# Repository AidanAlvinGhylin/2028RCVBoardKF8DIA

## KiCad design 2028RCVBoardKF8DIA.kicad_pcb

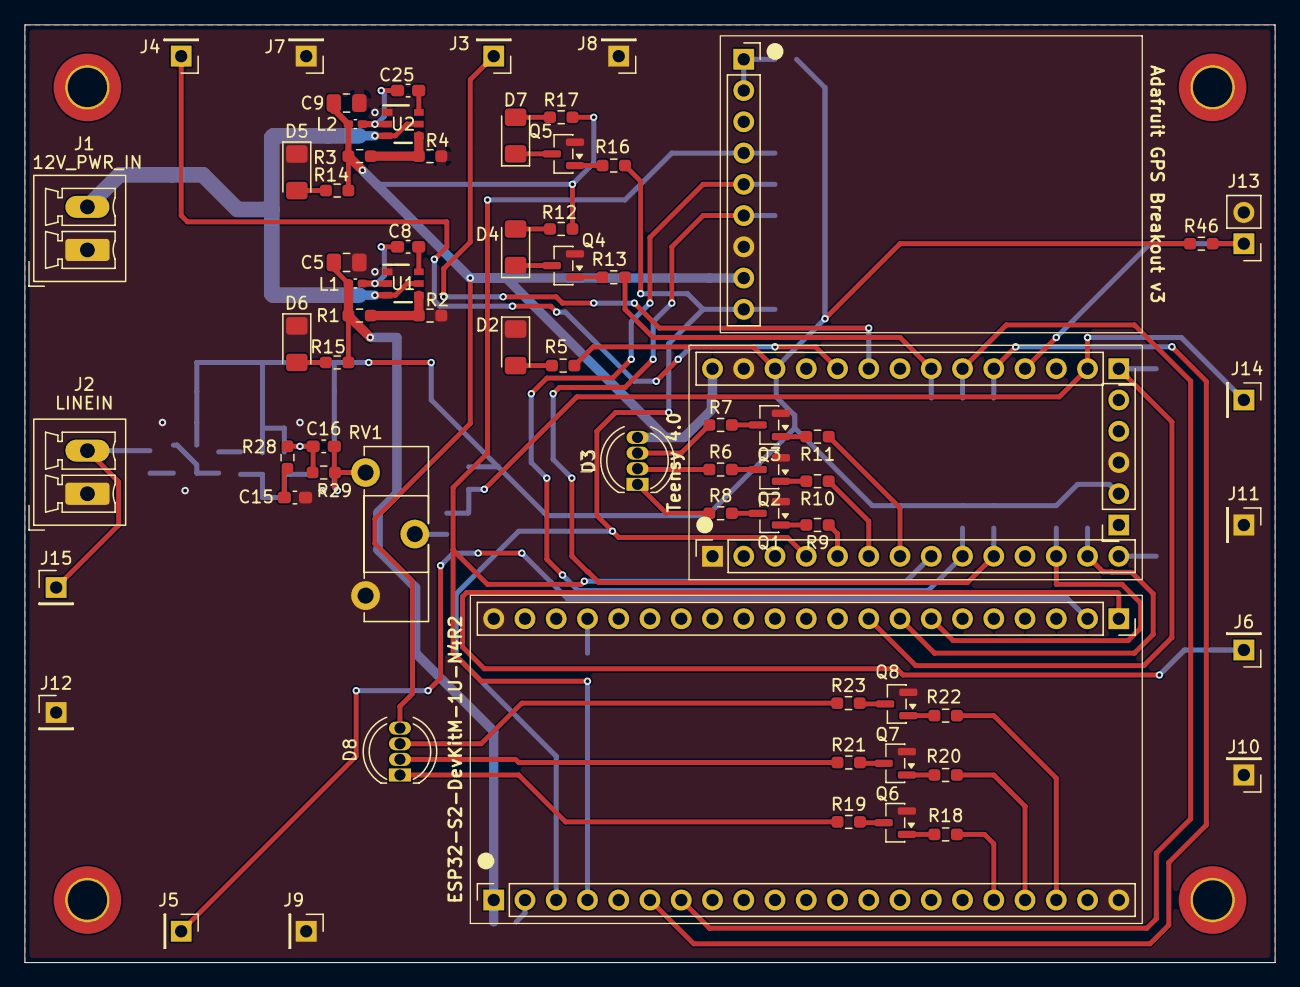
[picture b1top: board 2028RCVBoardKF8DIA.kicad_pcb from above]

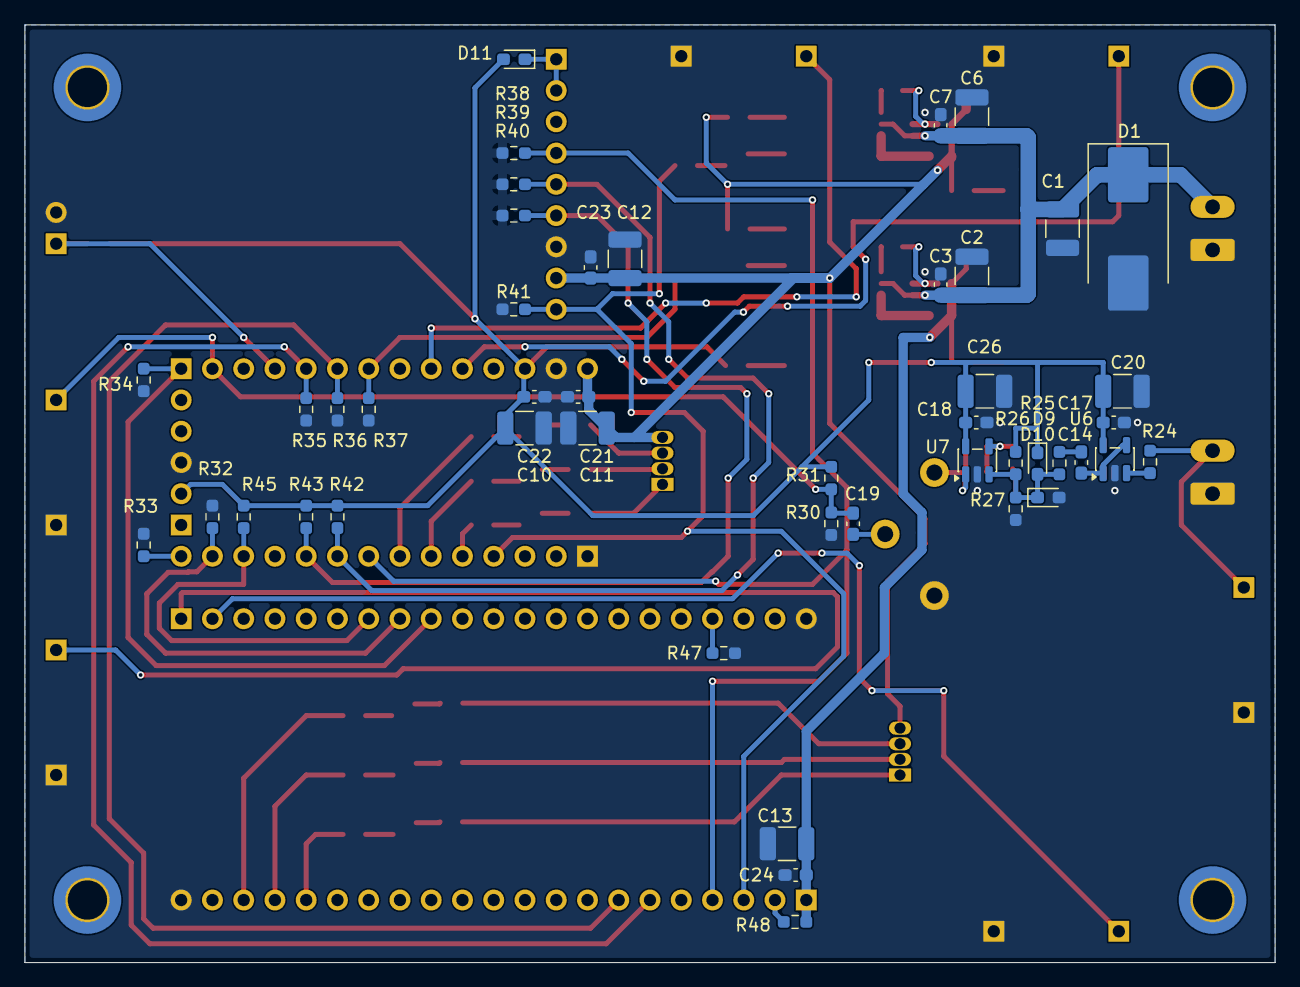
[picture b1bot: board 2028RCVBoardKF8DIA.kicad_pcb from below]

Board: 2 copper layers, 101.6 x 76.2 mm, 116 parts (46 on the bottom side), 73 nets.

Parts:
C1, C2, C6, C10, C11, C12, C13: 47uF; C_1210_3225Metric_Pad1.33x2.70mm_HandSolder
C3, C7, C8, C21, C22, C23, C24, C25: 0.1uF; C_0603_1608Metric_Pad1.08x0.95mm_HandSolder
C5, C9: 22uF; C_0805_2012Metric_Pad1.18x1.45mm_HandSolder
C14, C15, C19: 10uF; C_0603_1608Metric_Pad1.08x0.95mm_HandSolder
C16: 10nF; C_0603_1608Metric_Pad1.08x0.95mm_HandSolder
C17, C18: 100nF; C_0603_1608Metric_Pad1.08x0.95mm_HandSolder
C20, C26: 4.7uF; C_1210_3225Metric_Pad1.33x2.70mm_HandSolder
D1: D; D_SMC_Handsoldering
D2: 3V3_TNSY LED; LED_1206_3216Metric_Pad1.42x1.75mm_HandSolder
D3: Teensy Indicator LED; LED_D5.0mm-4_RGB
D4: GPS_LOCK LED; LED_1206_3216Metric_Pad1.42x1.75mm_HandSolder
D5: 5V LED; LED_1206_3216Metric_Pad1.42x1.75mm_HandSolder
D6: 3V3 LED; LED_1206_3216Metric_Pad1.42x1.75mm_HandSolder
D7: LED; LED_1206_3216Metric_Pad1.42x1.75mm_HandSolder
D8: ESP Indicator LED; LED_D5.0mm-4_RGB
D9, D10, D11: D_Schottky; D_0603_1608Metric_Pad1.05x0.95mm_HandSolder
J1: 12V_PWR_IN; PhoenixContact_MCV_1,5_2-G-3.5_1x02_P3.50mm_Vertical
J2: LINEIN; PhoenixContact_MCV_1,5_2-G-3.5_1x02_P3.50mm_Vertical
J3, J4, J5, J6, J7, J8, J9, J10, J11, J12, J14, J15: Conn_01x01; PinHeader_1x01_P2.54mm_Vertical
J13: Conn_01x02; PinHeader_1x02_P2.54mm_Vertical
L1, L2: 1.5uH; L_0402_1005Metric_Pad0.77x0.64mm_HandSolder
Q1, Q2, Q3, Q4, Q5, Q6, Q7, Q8: 2N7002; SOT-23
R1: 470; R_0603_1608Metric_Pad0.98x0.95mm_HandSolder
R2, R4: 100; R_0603_1608Metric_Pad0.98x0.95mm_HandSolder
R3, R6, R21, R29: 750; R_0603_1608Metric_Pad0.98x0.95mm_HandSolder
R5, R17: 2.2k; R_0603_1608Metric_Pad0.98x0.95mm_HandSolder
R7, R23: 220; R_0603_1608Metric_Pad0.98x0.95mm_HandSolder
R8, R19: 536; R_0603_1608Metric_Pad0.98x0.95mm_HandSolder
R9, R10, R11, R13, R16, R18, R20, R22, R30, R31, R32, R33, R34, R35, R36, R37, R38, R39, R40, R41, R42, R43, R45, R46, R47, R48: 10k; R_0603_1608Metric_Pad0.98x0.95mm_HandSolder
R12, R14, R15: 3.3k; R_0603_1608Metric_Pad0.98x0.95mm_HandSolder
R24, R25, R28: 1k; R_0603_1608Metric_Pad0.98x0.95mm_HandSolder
R26, R27: 240k; R_0603_1608Metric_Pad0.98x0.95mm_HandSolder
RV1: 1k; Potentiometer_ACP_CA14-H4_Horizontal
U1, U2: TPS563249DDCR; DDC0006A_L
U3: Teensy4.0_THT
U4: AdafruitGPSBreakoutv3_THT
U5: ESP32-S2-DevKitM-1U-N4R2
U6, U7: LT6015xS5; SOT-23-5

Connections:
3V3_GPS: D11.1 (K), U4.1 (3V3), U4.2 (EN)
3V3_TNSY: C10.2, C17.2, C18.2, C20.2, C22.2, C26.2, D9.1 (K), D11.2 (A), R5.1, R26.2, R31.2, R42.1, R43.1, R45.1, R46.1, U3.26 (3V3), U3.30 (3V3), U6.5 (V+), U7.5 (V+)
+3.3V: C5.1, C13.1, C24.1, L1.2, R1.1, R15.1, R48.1, U5.1 (3V3)
+5V: C9.1, C11.2, C12.1, C21.2, C23.1, D3.4 (BA), D8.4 (BA), L2.2, R3.1, R12.1, R14.1, R17.1, U3.28 (VIN), U4.8 (VIN)
+12V: C1.1, C2.1, C3.1, C6.1, C7.1, D1.1 (K), J1.2, U1.3 (VIN), U1.5 (EN), U2.3 (VIN), U2.5 (EN)
ADC_IN: C19.2, J14.1 (Pin_1_1), R30.2, R31.1, U3.16 (14/A0)
ADC_SMPL: J3.1 (Pin_1_1), U3.23 (21/A7)
ADC_SMPL_EN: J13.1, R46.2, U3.18 (16/A2)
DMA_TRAN: J4.1 (Pin_1_1), U3.24 (22/A8)
ESP_CS: R45.2, U3.12 (10/CS), U5.28 (34/FSPICS0)
ESP_LED_B: R22.1, U5.19 (17/ADC2_CH6/DAC_1)
ESP_LED_G: R20.1, U5.18 (16/ADC2_CH5)
ESP_LED_R: R18.1, U5.17 (15/ADC2_CH4)
ESP_MISO: R33.1, U3.14 (12/MISO), U5.31 (37/FSPIQ)
ESP_MOSI: R32.1, U3.13 (11/MOSI), U5.29 (35/FSPID)
ESP_SCLK: R34.1, U3.15 (13/SCLK), U5.30 (36/FSPICLK)
ESP_TNSY_HSK: R36.1, U3.20 (18/A4), U5.7 (5/ADC1_CH4)
GND: C1.2, C2.2, C3.2, C5.2, C6.2, C7.2, C9.2, C10.1, C11.1, C12.2, C13.2, C15.1, C17.1, C18.1, C20.1, C21.1, C22.1, C23.2, C24.2, C26.1, D1.2 (A), D2.1 (K), D5.1 (K), D6.1 (K), D10.2 (A), J1.1, J2.1, J7.1 (Pin_1_1), J8.1 (Pin_1_1), J9.1 (Pin_1_1), J10.1 (Pin_1_1), J11.1 (Pin_1_1), J12.1 (Pin_1_1), J13.2, Q1.2 (S), Q2.2 (S), Q3.2 (S), Q4.2 (S), Q5.2 (S), Q6.2 (S), Q7.2 (S), Q8.2 (S), R2.1, R4.1, R27.1, R30.1, R32.2, R33.2, R34.2, R35.2, R36.2, R37.2, R38.1, R39.1, R40.1, R41.1, R47.2, RV1.3, U1.1 (GND), U2.1 (GND), U3.1 (GND), U3.27 (GND), U3.31 (GND), U4.7 (GND), U5.21 (GND), U5.42 (GND), U6.2 (V-), U7.2 (V-)
GPS_FIX: R38.2, U3.8 (6), U4.4 (FIX), U5.4 (2/ADC1_CH1)
GPS_LOCK: R13.1, R37.1, U3.21 (19/A5)
GPS_PPS: R16.1, R41.2, U3.4 (2), U4.9 (PPS), U5.3 (1/ADC1_CH0)
GPS_TNSY_UART: R39.2, R42.2, U3.9 (7/RX2), U4.5 (TX)
HTTP_POST: J5.1 (Pin_1_1), U5.23 (19/ADC2_CH8)
LINEIN: J2.2, J15.1 (Pin_1_1), R24.1
unnamed: C14.2, R25.1
unnamed: C15.2, R28.1
unnamed: C16.2, R29.2, RV1.1, U7.1
unnamed: C19.1, RV1.2
unnamed: D2.2 (A), R5.2
unnamed: D3.3 (BK), R7.1
unnamed: D3.2 (GK), R6.1
unnamed: D3.1 (RK), R8.1
unnamed: D4.2 (A), R12.2
unnamed: D4.1 (K), Q4.3 (D)
unnamed: D5.2 (A), R14.2
unnamed: D6.2 (A), R15.2
unnamed: D7.2 (A), R17.2
unnamed: D7.1 (K), Q5.3 (D)
unnamed: D8.3 (BK), R23.1
unnamed: D8.2 (GK), R21.1
unnamed: D8.1 (RK), R19.1
unnamed: D9.2 (A), D10.1 (K), R25.2, R26.1, R27.2, U7.3 (+)
unnamed: Q1.3 (D), R8.2
unnamed: Q1.1 (G), R9.2
unnamed: Q2.3 (D), R6.2
unnamed: Q2.1 (G), R10.2
unnamed: Q3.3 (D), R7.2
unnamed: Q3.1 (G), R11.2
unnamed: Q4.1 (G), R13.2
unnamed: Q5.1 (G), R16.2
unnamed: Q6.3 (D), R19.2
unnamed: Q6.1 (G), R18.2
unnamed: Q7.3 (D), R21.2
unnamed: Q7.1 (G), R20.2
unnamed: Q8.3 (D), R23.2
unnamed: Q8.1 (G), R22.2
unnamed: C8.2, L1.1, U1.2 (SW)
unnamed: C8.1, U1.6 (VBST)
unnamed: R1.2, R2.2, U1.4 (VFB)
unnamed: C25.2, L2.1, U2.2 (SW)
unnamed: C25.1, U2.6 (VBST)
unnamed: R3.2, R4.2, U2.4 (VFB)
unnamed: R48.2, U5.2 (0)
unnamed: R47.1, U5.39 (45)
unnamed: R24.2, U6.3 (+)
unnamed: C14.1, U6.1, U6.4 (-)
unnamed: C16.1, R28.2, R29.1, U7.4 (-)
SPI_RX: J6.1 (Pin_1_1), U5.22 (18/ADC2_CH7/DAC_2)
TNSY_ESP_HSK: R35.1, U3.19 (17/A3), U5.6 (4/ADC1_CH3)
TNSY_GPS_UART: R40.2, R43.2, U3.10 (8/TX2), U4.6 (RX)
TNSY_LED_B: R11.1, U3.7 (5)
TNSY_LED_G: R10.1, U3.6 (4)
TNSY_LED_R: R9.1, U3.5 (3)
